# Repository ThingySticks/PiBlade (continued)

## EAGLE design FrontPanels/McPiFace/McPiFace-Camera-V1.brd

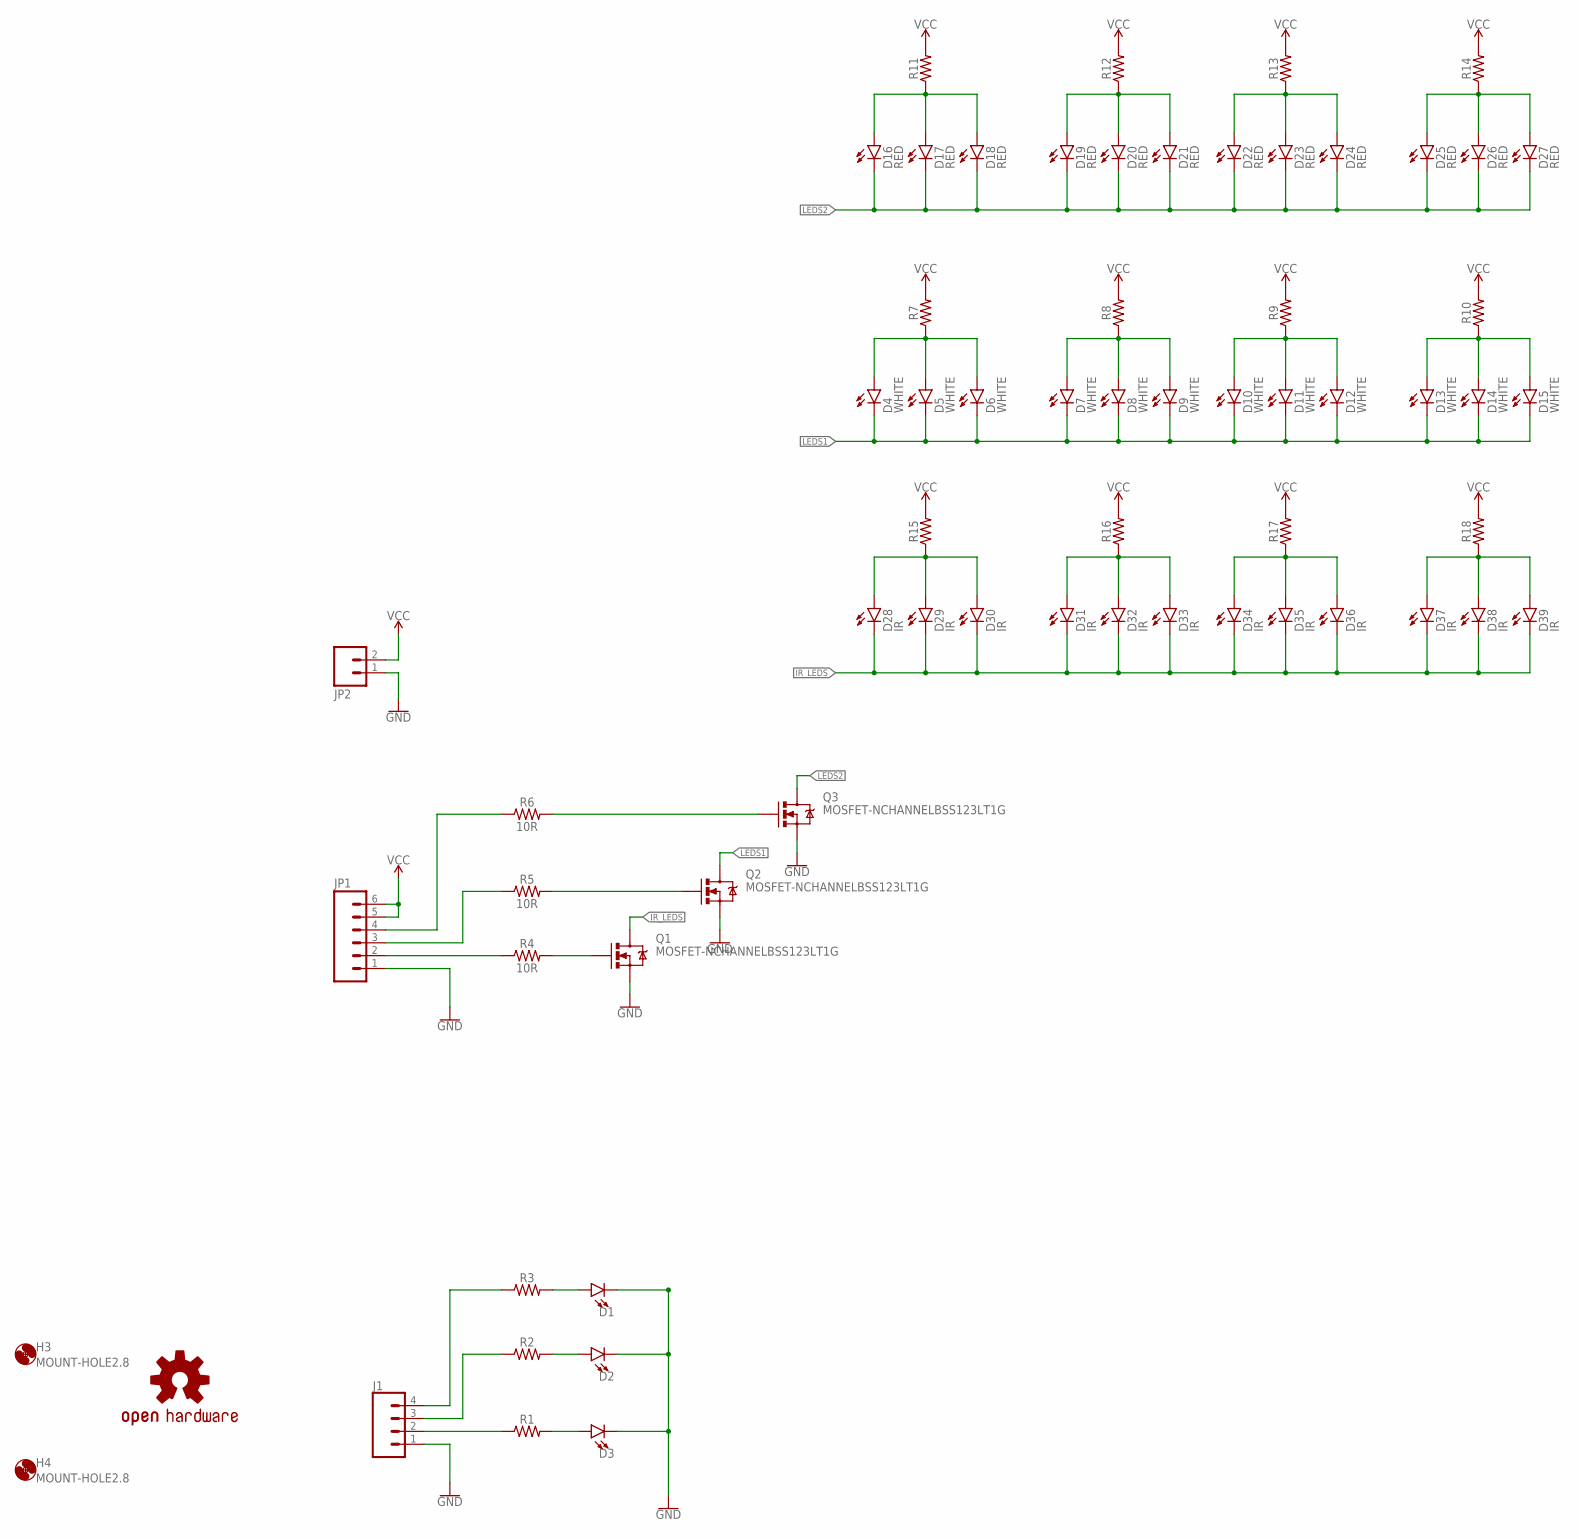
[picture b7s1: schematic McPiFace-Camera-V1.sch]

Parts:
D1, D2, D3: LED1206-BOTTOM-1.6MM; LED-1206-BOTTOM-1.6MM
D4, D5, D6, D7, D8, D9, D10, D11, D12, D13, D14, D15: WHITE; LED-1206
D16, D17, D18, D19, D20, D21, D22, D23, D24, D25, D26, D27: RED; LED-1206
D28, D29, D30, D31, D32, D33, D34, D35, D36, D37, D38, D39: IR; LED-1206
H3, H4: MOUNT-HOLE2.8; 2,8
J1: CONN_04SMD2; 1X04_1MM_RA
JP1: M06SMD-1MM; 1X06-1MM
JP2: M02-JST-2MM-SMT; JST-2-SMD
LOGO1: OSHW-LOGOL; OSHW-LOGO-L
Q1, Q2, Q3: MOSFET-NCHANNELBSS123LT1G; SOT23-3
R1, R2, R3, R7, R8, R9, R10, R11, R12, R13, R14, R15, R16, R17, R18: 1206
R4, R5, R6: 10R; 1206

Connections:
GND: D1.C, D2.C, D3.C, J1.1, JP1.1, JP2.1 (2), Q1.2 (S), Q2.2 (S), Q3.2 (S)
IR_LEDS: D28.C, D29.C, D30.C, D31.C, D32.C, D33.C, D34.C, D35.C, D36.C, D37.C, D38.C, D39.C, Q1.3 (D)
LEDS1: D4.C, D5.C, D6.C, D7.C, D8.C, D9.C, D10.C, D11.C, D12.C, D13.C, D14.C, D15.C, Q2.3 (D)
LEDS2: D16.C, D17.C, D18.C, D19.C, D20.C, D21.C, D22.C, D23.C, D24.C, D25.C, D26.C, D27.C, Q3.3 (D)
unnamed: D1.A, R3.2
unnamed: D2.A, R2.2
unnamed: D3.A, R1.2
unnamed: J1.2, R1.1
unnamed: J1.3, R2.1
unnamed: J1.4, R3.1
unnamed: JP1.2, R4.1
unnamed: JP1.3, R5.1
unnamed: JP1.4, R6.1
unnamed: Q3.1 (G), R6.2
unnamed: Q2.1 (G), R5.2
unnamed: Q1.1 (G), R4.2
unnamed: D13.A, D14.A, D15.A, R10.1
unnamed: D10.A, D11.A, D12.A, R9.1
unnamed: D7.A, D8.A, D9.A, R8.1
unnamed: D4.A, D5.A, D6.A, R7.1
unnamed: D16.A, D17.A, D18.A, R11.1
unnamed: D19.A, D20.A, D21.A, R12.1
unnamed: D22.A, D23.A, D24.A, R13.1
unnamed: D25.A, D26.A, D27.A, R14.1
unnamed: D28.A, D29.A, D30.A, R15.1
unnamed: D31.A, D32.A, D33.A, R16.1
unnamed: D34.A, D35.A, D36.A, R17.1
unnamed: D37.A, D38.A, D39.A, R18.1
VCC: JP1.5, JP1.6, JP2.2 (1), R7.2, R8.2, R9.2, R10.2, R11.2, R12.2, R13.2, R14.2, R15.2, R16.2, R17.2, R18.2

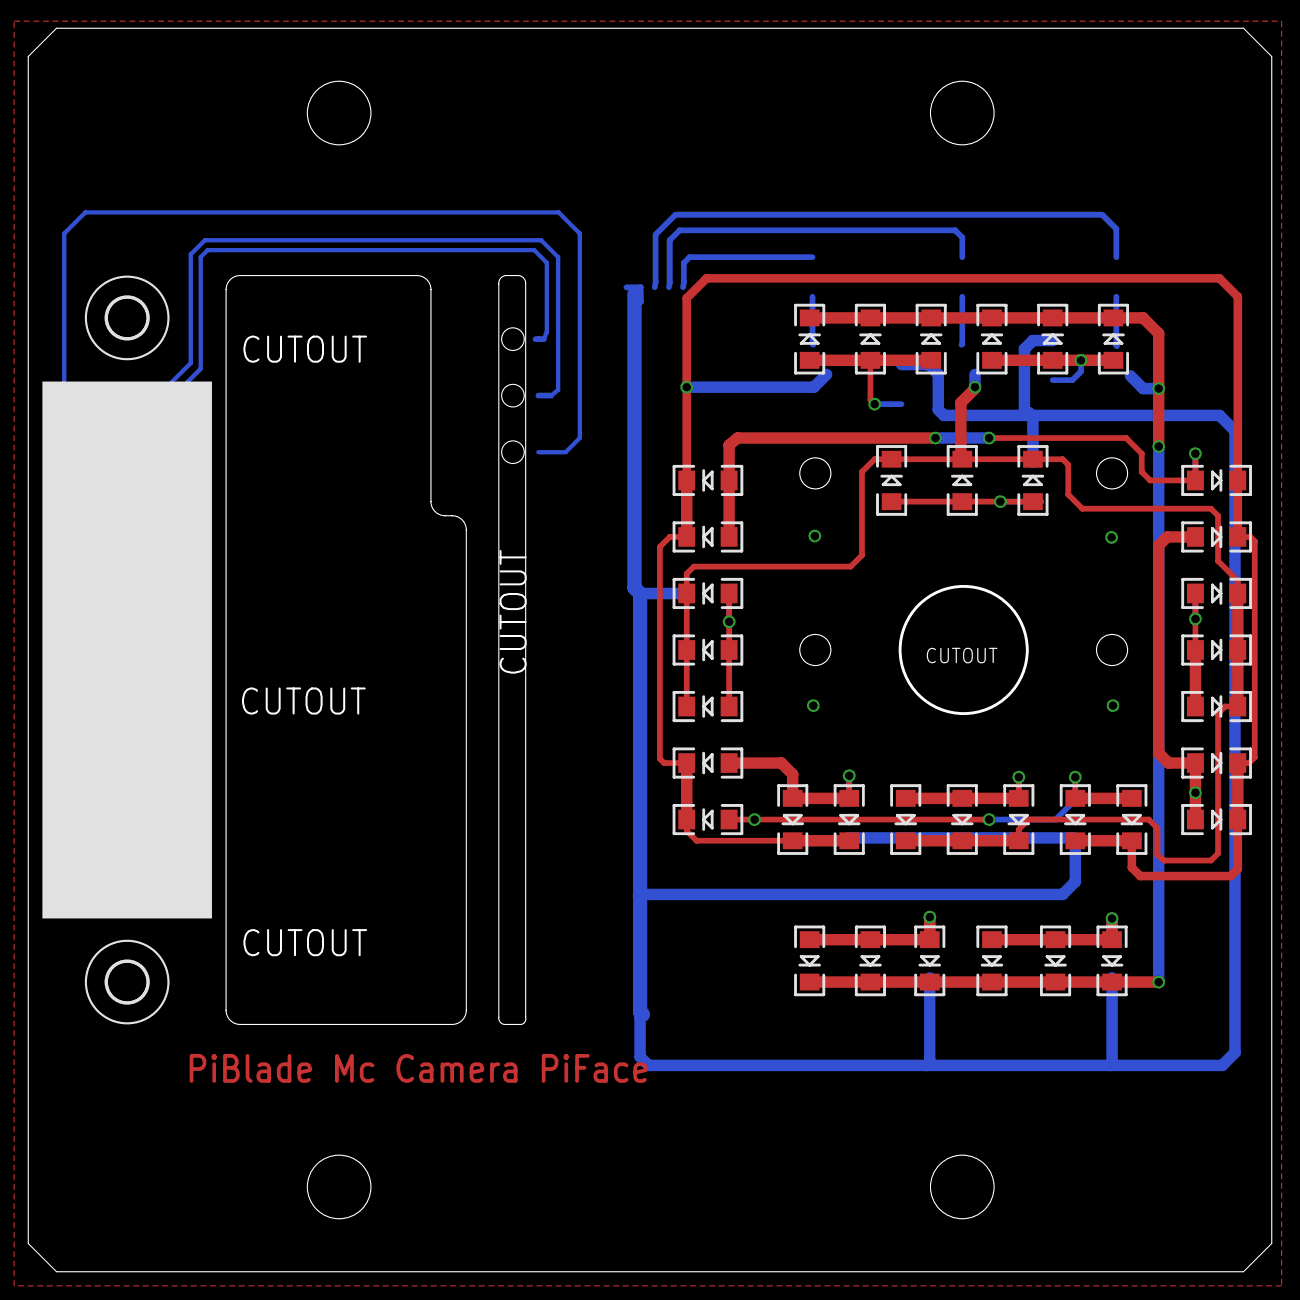
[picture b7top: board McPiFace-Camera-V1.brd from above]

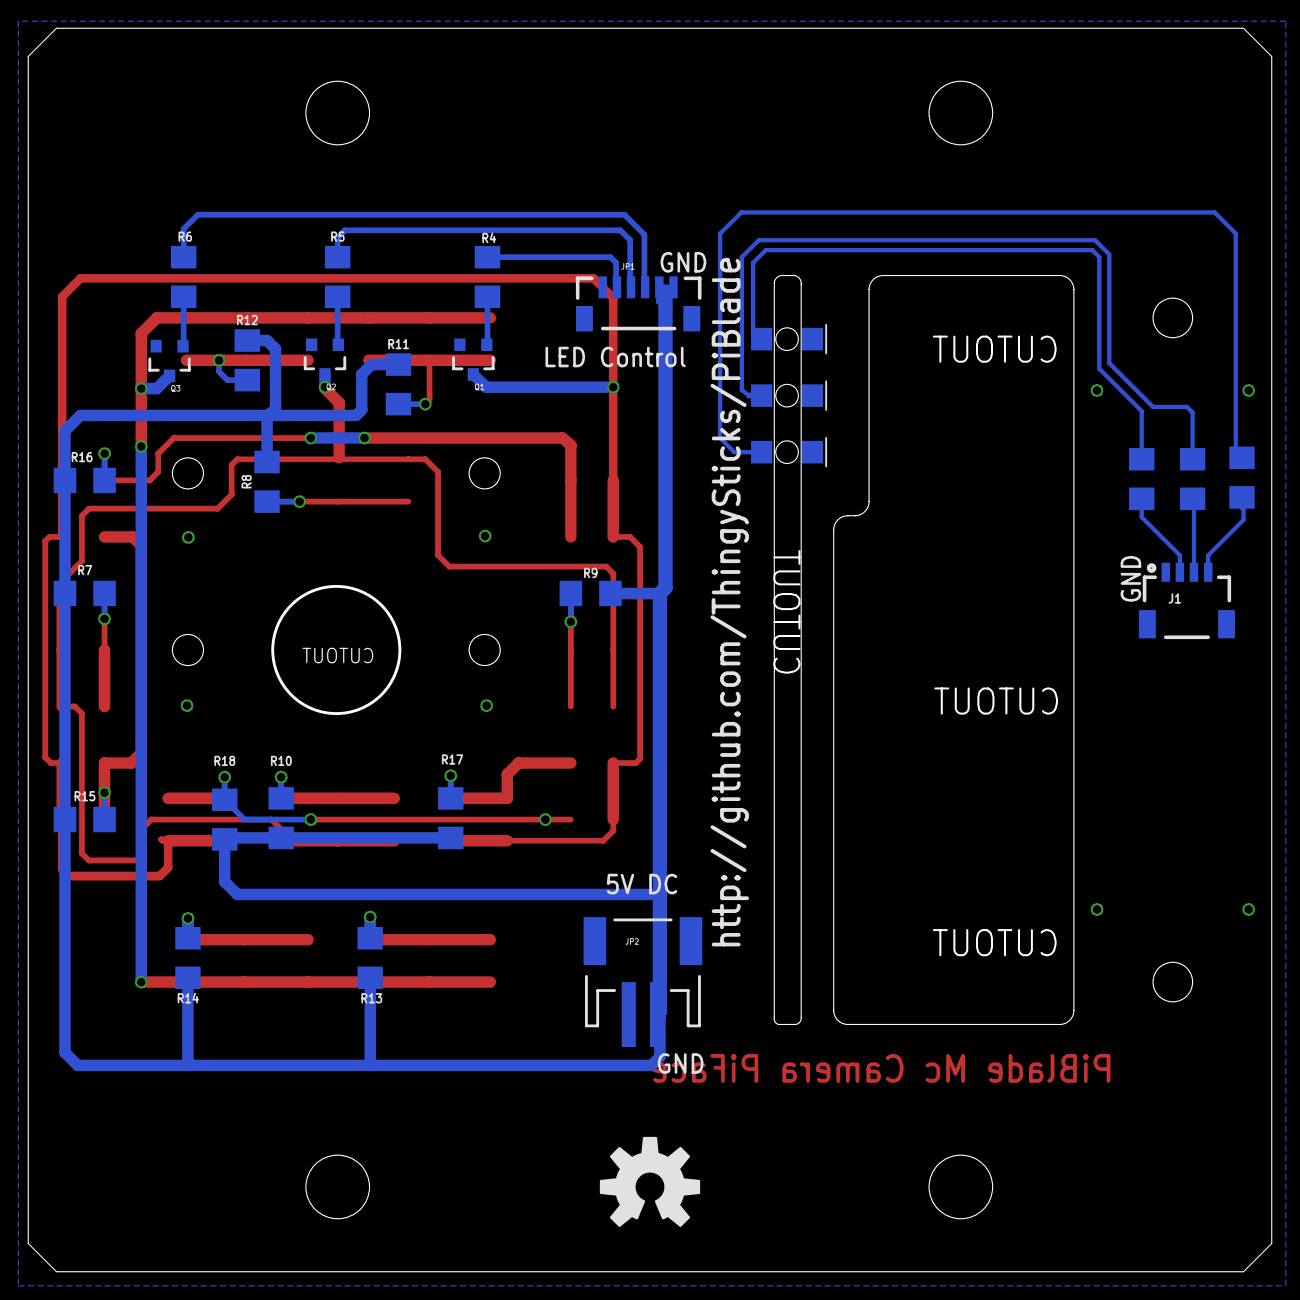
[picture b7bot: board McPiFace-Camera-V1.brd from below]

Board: 2 copper layers, 88.0 x 88.0 mm, 66 parts (28 on the bottom side), 29 nets.

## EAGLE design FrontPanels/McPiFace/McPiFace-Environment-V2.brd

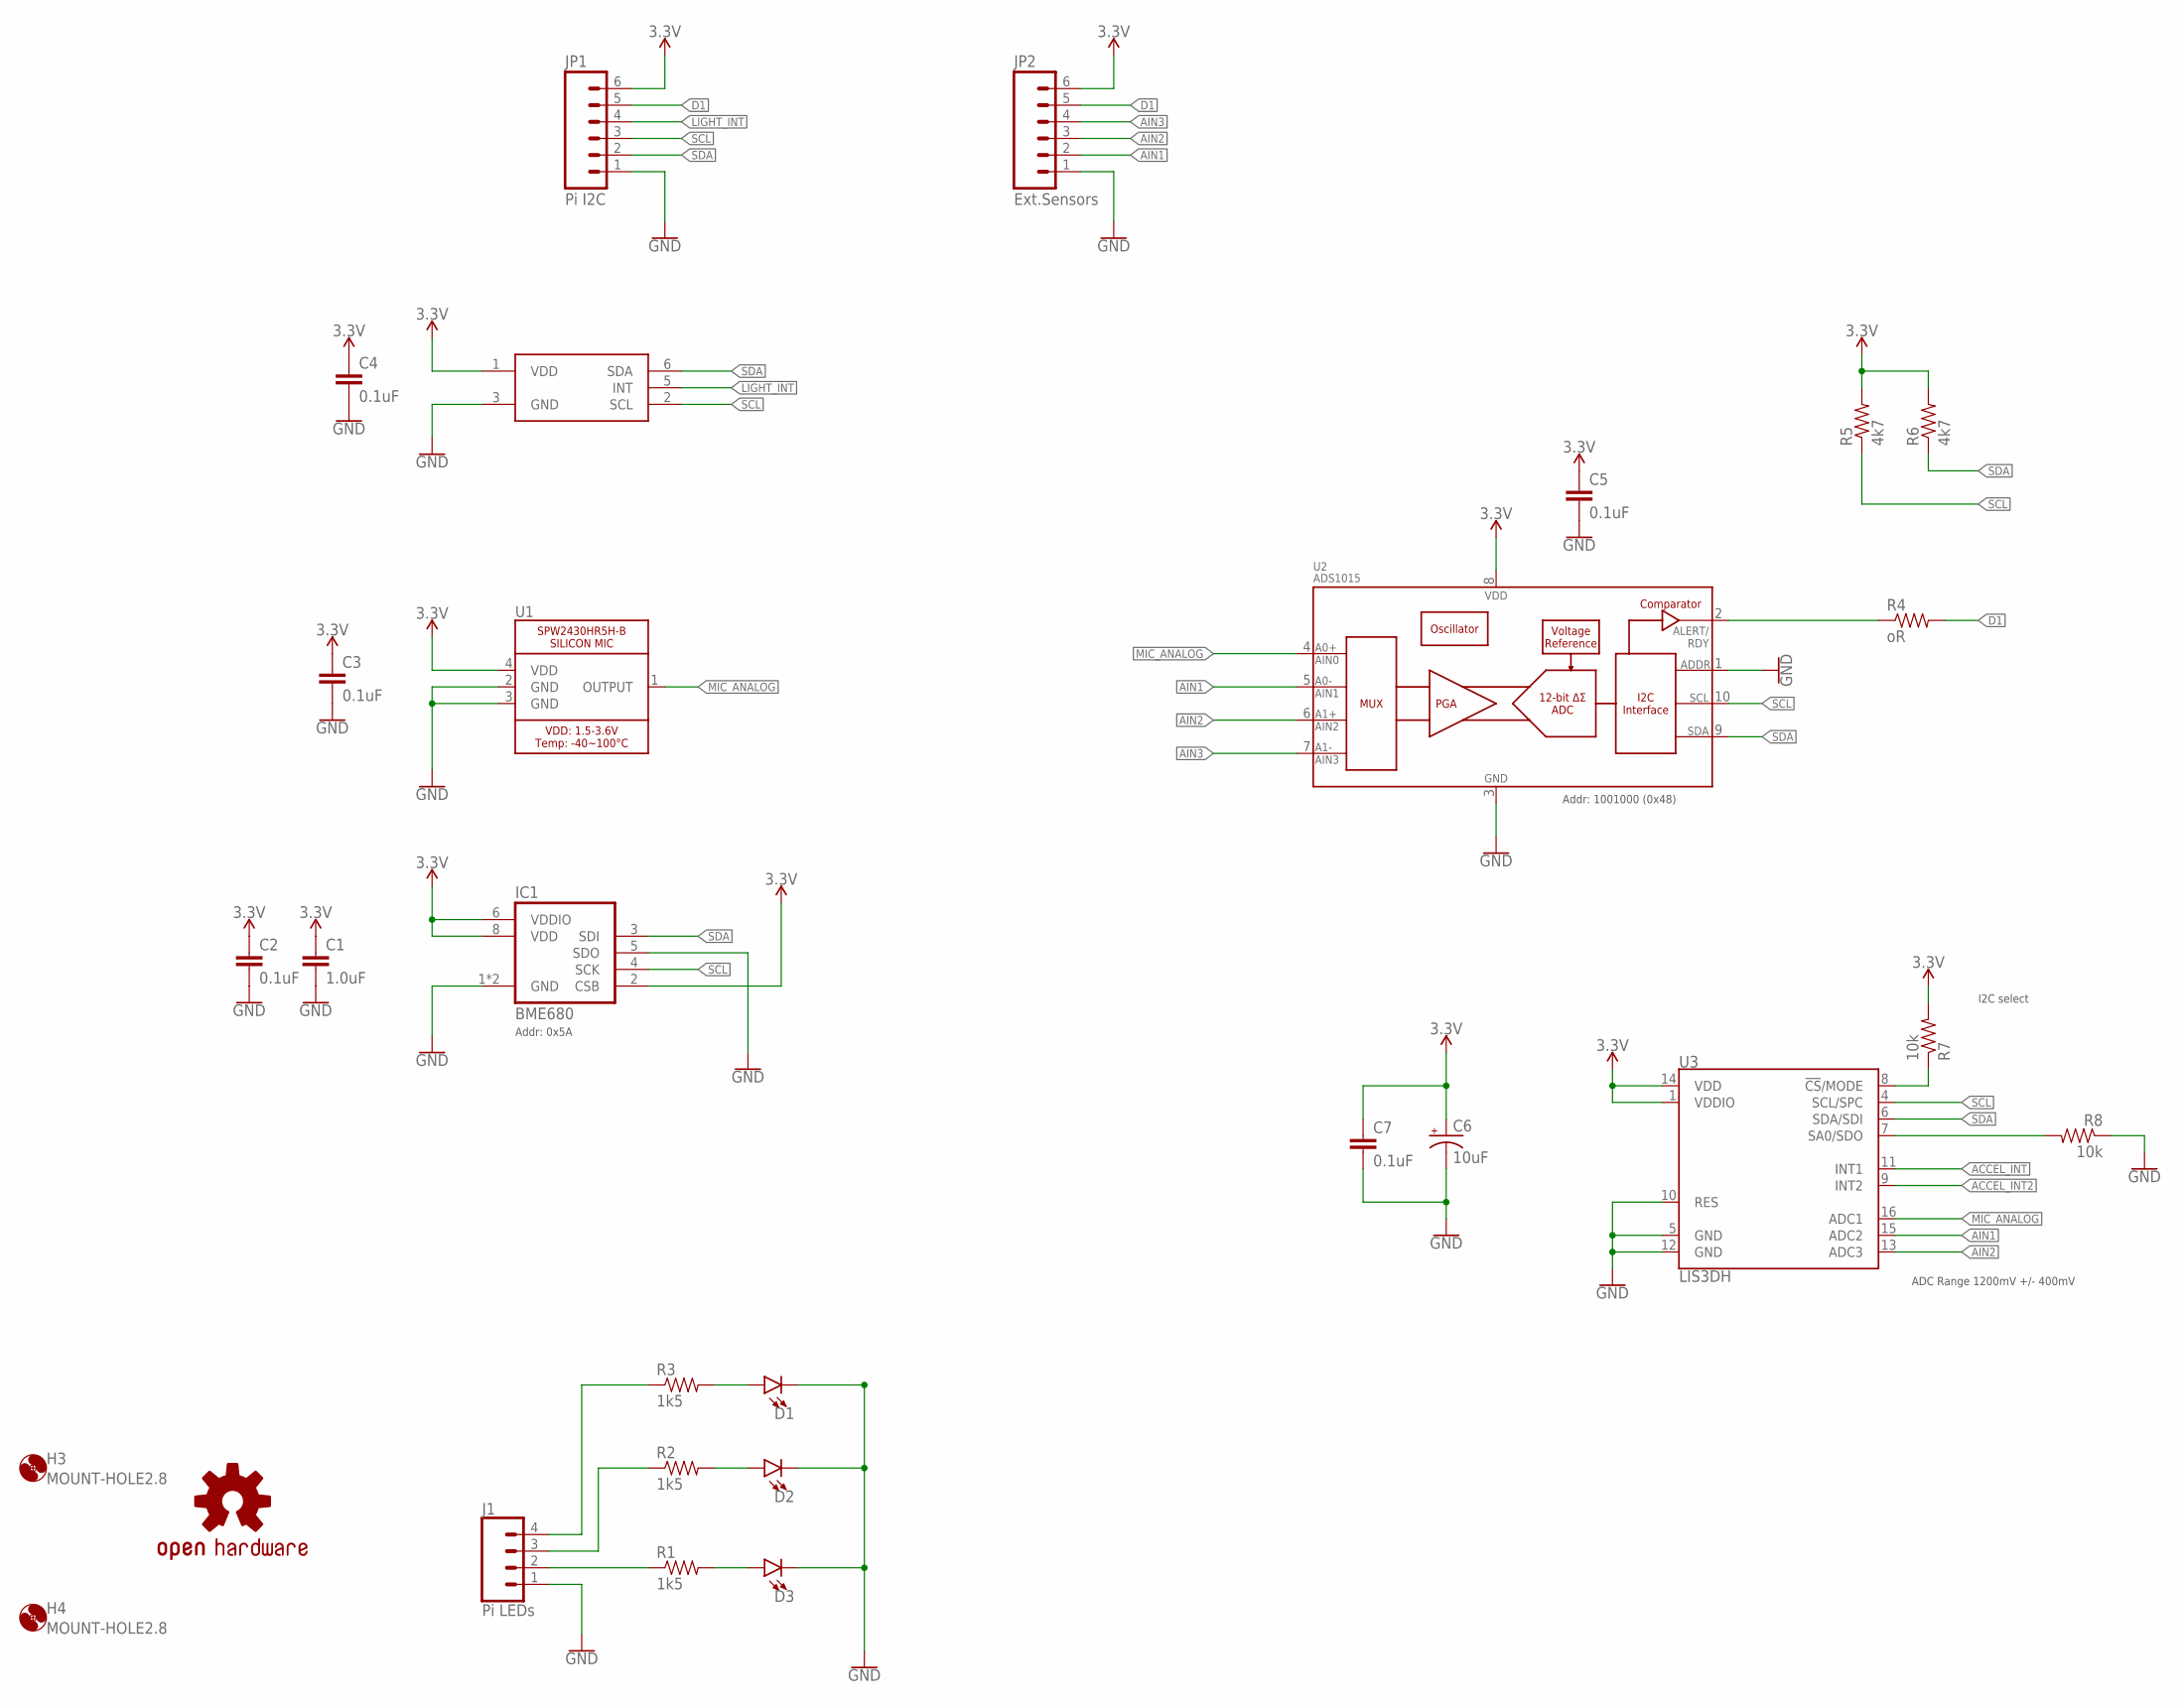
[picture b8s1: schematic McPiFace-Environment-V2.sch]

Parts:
C1: 1.0uF; 0805
C2, C3, C4, C5, C7: 0.1uF; 0805
C6: 10uF; EIA3216
D1, D2, D3: LED1206-BOTTOM-1.6MM; LED-1206-BOTTOM-1.6MM
H3, H4: MOUNT-HOLE2.8; 2,8
IC1: BME680
J1: Pi LEDs; 1X04_1MM_RA
JP1: Pi I2C; 1X06-1MM
JP2: Ext.Sensors; 1X06-1MM
LOGO1: OSHW-LOGOL; OSHW-LOGO-L
R1, R2, R3: 1k5; 0805
R4: oR; 0805
R5, R6: 4k7; 0805
R7, R8: 10k; 0805
U1: SPW2430HR5H-B
U2: ADS1015; MSOP10
U3: LIS3DH; LGA-16-3X3
U$1: TCS3472; FN-6

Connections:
3.3V: C1.1, C2.1, C3.1, C4.1, C5.1, C6.A (+), C7.1, IC1.2 (CSB), IC1.6 (VDDIO), IC1.8 (VDD), JP1.6, JP2.6, R5.2, R6.2, R7.2, U1.4 (VDD), U2.8 (VDD), U3.1 (VDDIO), U3.14 (VDD), U$1.1 (VDD)
ACCEL_INT: U3.11 (INT1)
ACCEL_INT2: U3.9 (INT2)
AIN1: JP2.2, U2.5 (AIN1), U3.15 (ADC2)
AIN2: JP2.3, U2.6 (AIN2), U3.13 (ADC3)
AIN3: JP2.4, U2.7 (AIN3)
ALERT: R4.1, U2.2 (ALERT/RDY)
D1: JP1.5, JP2.5, R4.2
GND: C1.2, C2.2, C3.2, C4.2, C5.2, C6.C (-), C7.2, D1.C, D2.C, D3.C, IC1.1 (GND), IC1.5 (SDO), IC1.7 (GND), J1.1, JP1.1, JP2.1, R8.1, U1.2 (GND), U1.3 (GND), U2.1 (ADDR), U2.3 (VSS), U3.5 (GND), U3.10 (RES), U3.12 (GND), U$1.3 (GND)
LIGHT_INT: JP1.4, U$1.5 (INT)
MIC_ANALOG: U1.1 (OUTPUT), U2.4 (AIN0), U3.16 (ADC1)
unnamed: D1.A, R3.2
unnamed: D2.A, R2.2
unnamed: D3.A, R1.2
unnamed: J1.2, R1.1
unnamed: J1.3, R2.1
unnamed: J1.4, R3.1
unnamed: R8.2, U3.7 (SA0/SDO)
unnamed: R7.1, U3.8 (!CS!/MODE)
SCL: IC1.4 (SCK), JP1.3, R5.1, U2.10 (SCL), U3.4 (SCL/SPC), U$1.2 (SCL)
SDA: IC1.3 (SDI), JP1.2, R6.1, U2.9 (SDA), U3.6 (SDA/SDI), U$1.6 (SDA)

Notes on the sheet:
Addr: 1001000 (0x48)
Addr: 0x5A
I2C select
ADC Range 1200mV +/- 400mV

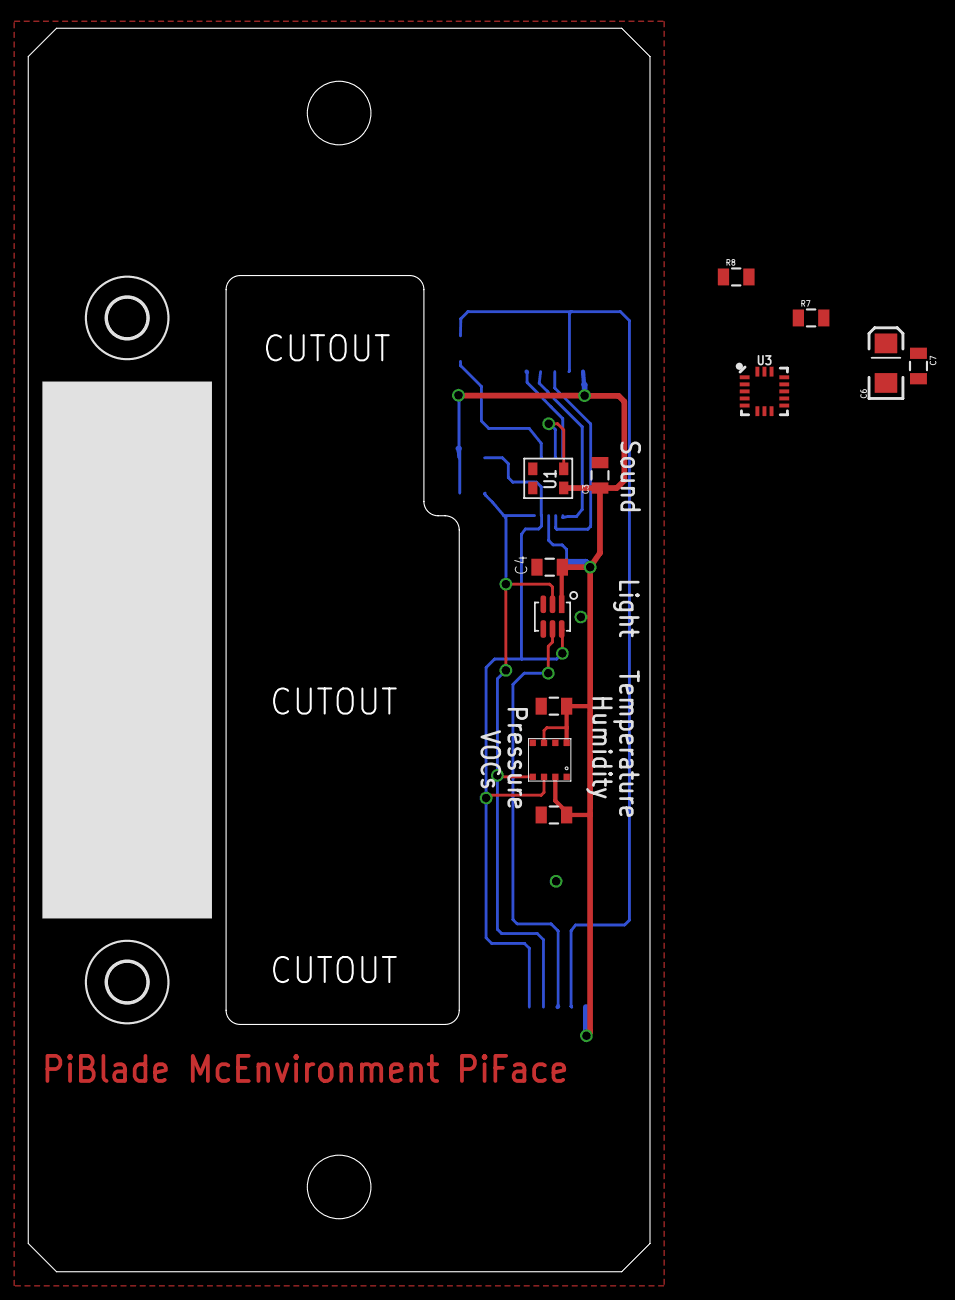
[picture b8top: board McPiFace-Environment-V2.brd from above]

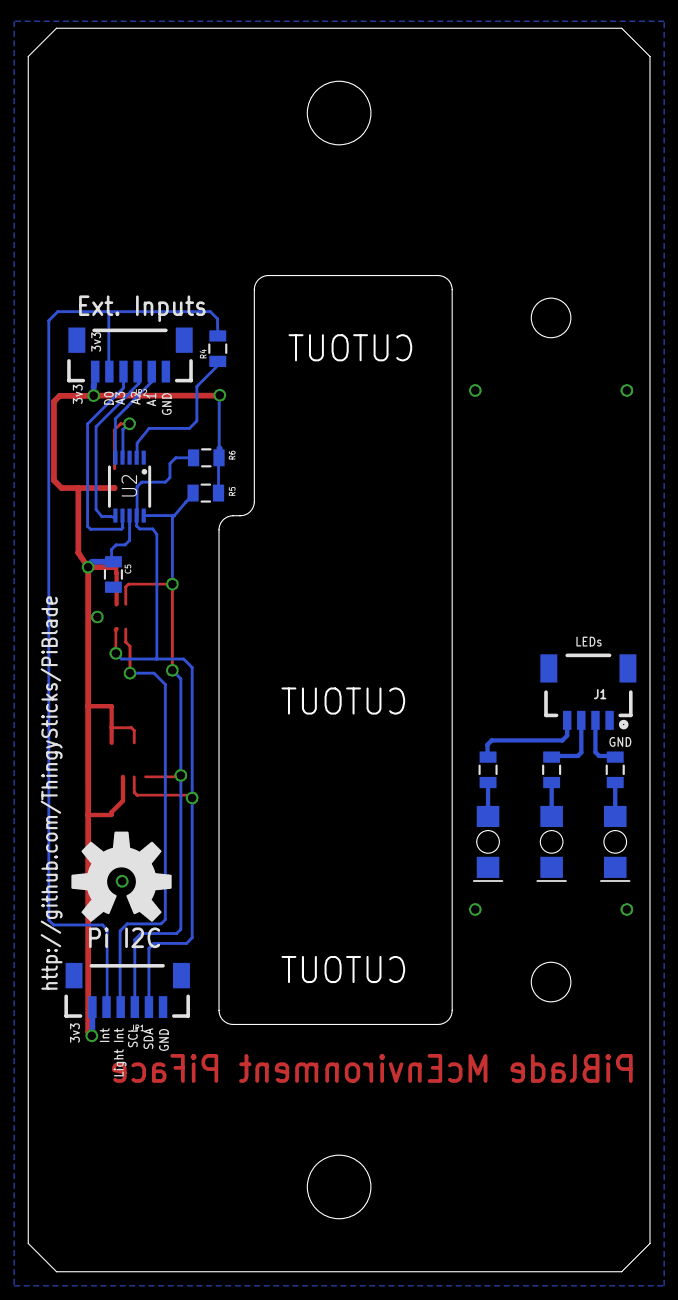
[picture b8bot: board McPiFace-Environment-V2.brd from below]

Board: 2 copper layers, 44.0 x 88.0 mm, 29 parts (15 on the bottom side), 19 nets.

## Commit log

2019-01-05 V1.1 PCB as send to DirtyPCBs. Increased mounting hole size, moved OSH symbol to PCB read.
2019-01-05 initial readme.
2019-01-05 Base for Raspberry Pi (tested with 3), to fit front panel.
2019-01-14 New PiFace front panels as sent to DirtyPCBs
2019-01-21 RGB LED panel.
    As sent to Dirty PCBs
2019-01-21 Environment monitor V1 as send to Dirty PCBs.
2019-01-21 Environment monitor V2 (maybe send to Dirty PCBs).
2019-01-21 Pi Camera panel as send to Dirty PCBs.
2019-01-21 RGB Seven Segment panel as send to Dirty PCBs.
2019-01-21 V2 fan panel as send to Dirty PCBs
2019-01-21 DC Input panel (as send to Dirty PCBs)
2019-01-21 Added Particle Feather Ethernet board (unchecked)
2019-01-21 Version 3 of fan controller with ATTiny85 to control and accelerometer to check for fan vibration (+ it includes a temperature sensor)
2019-01-21 Fixed height of ethernet connector.
    Moved LEDs/connector as the frame clashes with that area of the panel.
2019-01-21 Update PSU input board: * Added LEDs. * Moved DC Jack input to a lower position to align with the USB board better.
    Updated DirtyPCBs
2019-01-22 Added PCB images from DirtyPCBs.
2019-01-22 2 Pi's back to back mount.
2019-01-25 Moved / Renamed PSU Input hat.
2019-01-25 Backplane connector board with various IO for front panels, additional power connectors and a breakout board.
2019-01-25 Start of back plane to distrubute power and RS485 bus.
2019-01-25 Front panel with mini oled display positioned to cover the USB connectors to prevent the USB ports being used.
2019-01-25 Front panel with 0.91" OLED display in place of the name label (and name label moved).
2019-01-25 Added images from schematic/pcbs and scripts to generate them.
2019-01-25 Added gitignore.
